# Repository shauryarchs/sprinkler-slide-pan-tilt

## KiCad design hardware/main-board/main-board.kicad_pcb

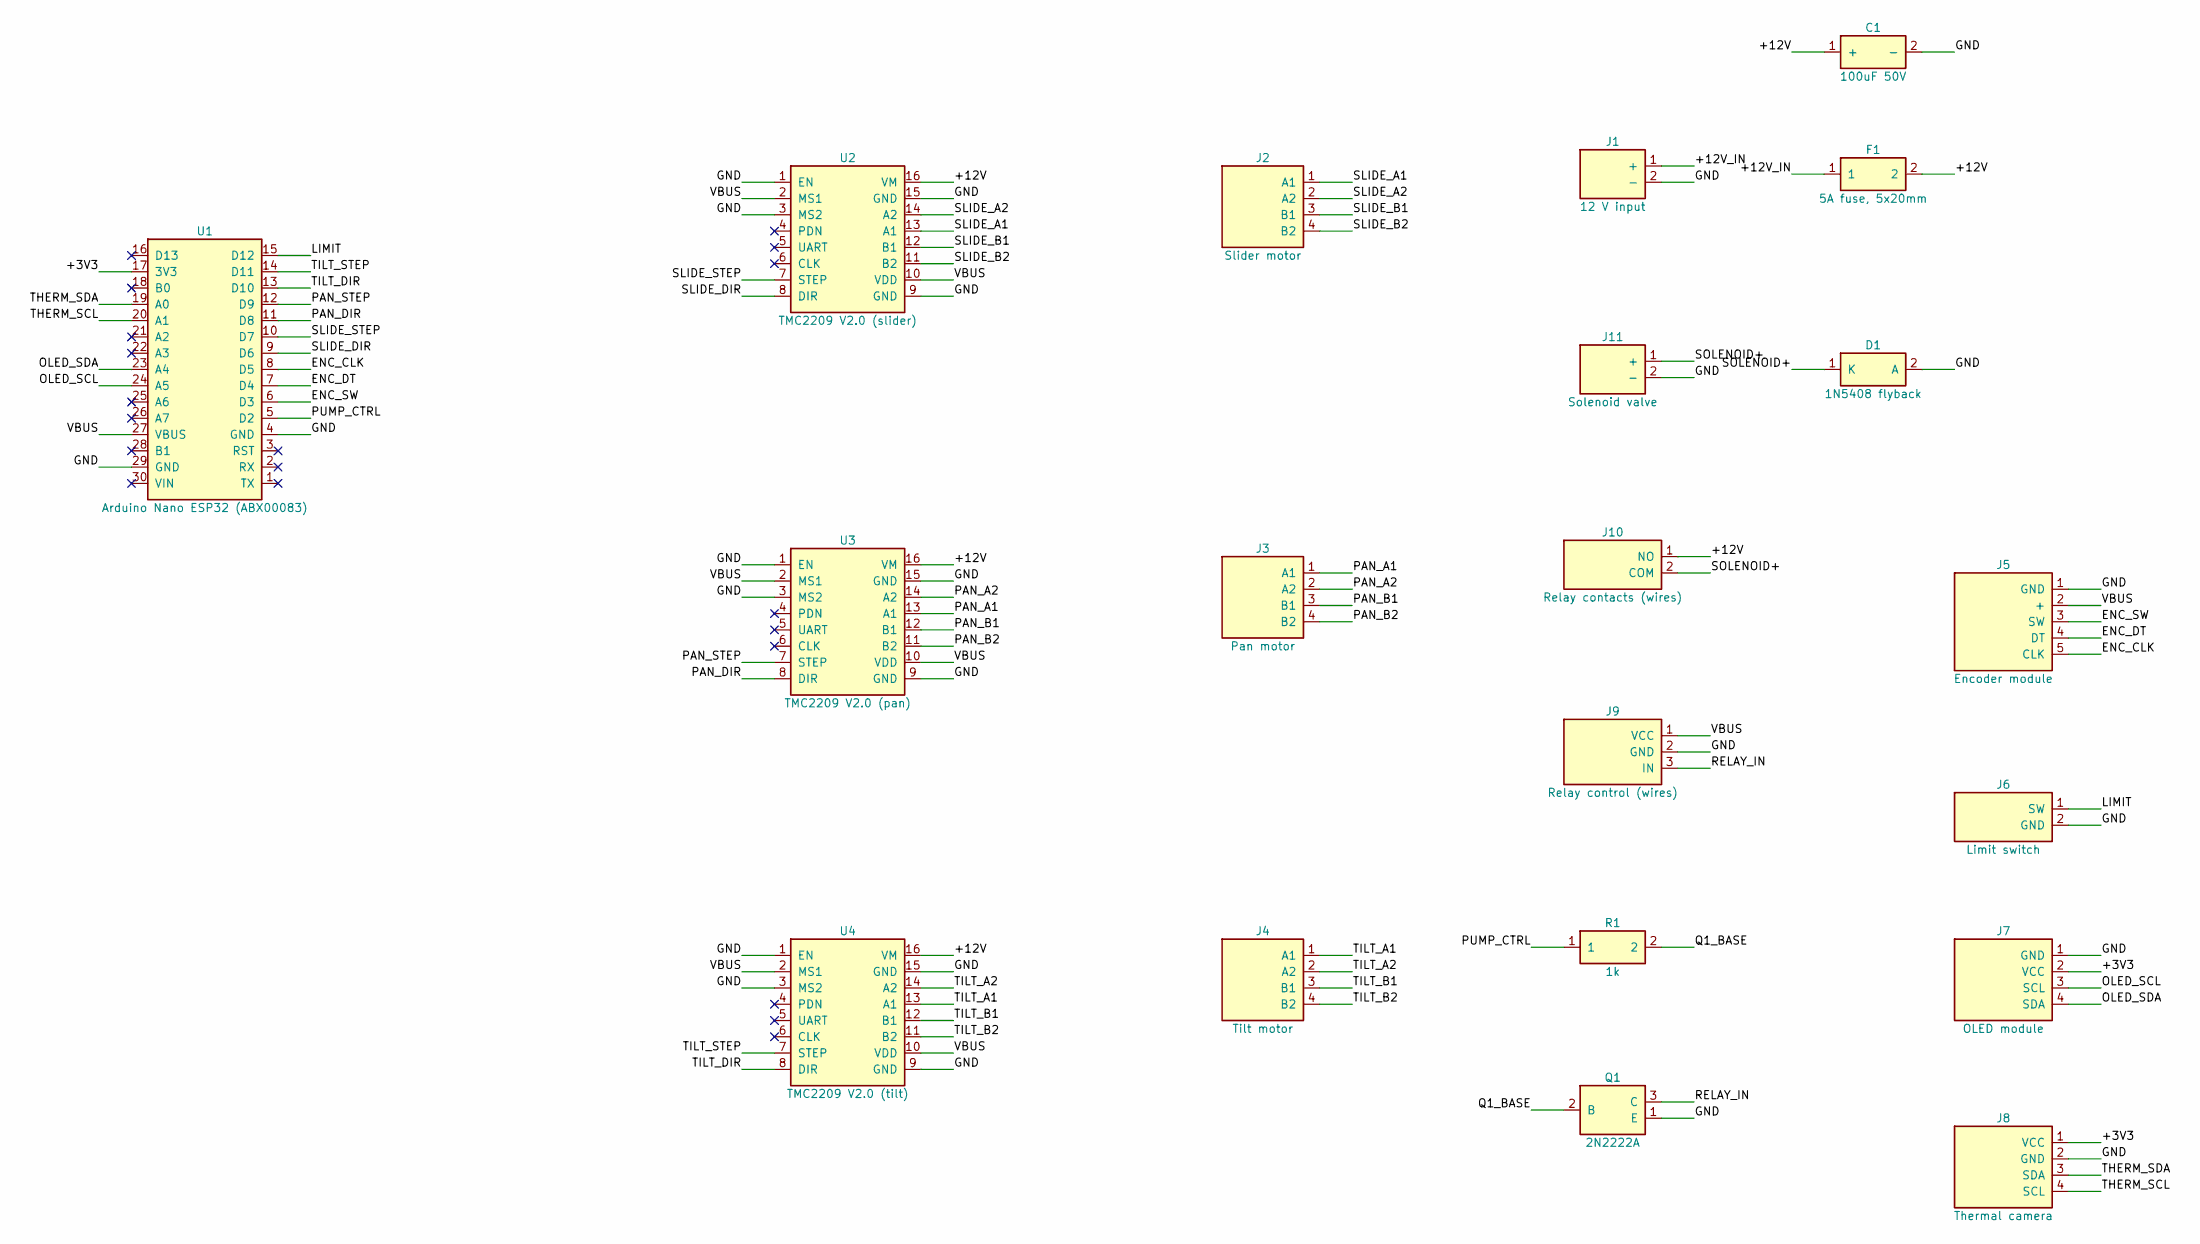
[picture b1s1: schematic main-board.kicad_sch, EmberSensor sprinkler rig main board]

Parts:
C1: 100uF 50V; CP_Radial_D8.0mm_P3.50mm
D1: 1N5408 flyback; D_DO-201AD_P15.24mm_Horizontal
F1: 5A fuse, 5x20mm; Fuseholder_Clip-5x20mm_Keystone_3517_Inline_P23.11x6.76mm_D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
J1: 12 V input; TerminalBlock_Phoenix_MKDS-1,5-2-5.08_1x02_P5.08mm_Horizont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
J2: Slider motor; TerminalBlock_Phoenix_MKDS-1,5-4-5.08_1x04_P5.08mm_Horizont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
J3: Pan motor; TerminalBlock_Phoenix_MKDS-1,5-4-5.08_1x04_P5.08mm_Horizont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
J4: Tilt motor; TerminalBlock_Phoenix_MKDS-1,5-4-5.08_1x04_P5.08mm_Horizont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
J5: Encoder module; PinHeader_1x05_P2.54mm_Vertical
J6: Limit switch; JST_XH_B2B-XH-A_1x02_P2.50mm_Vertical
J7: OLED module; PinHeader_1x04_P2.54mm_Vertical
J8: Thermal camera; JST_XH_B4B-XH-A_1x04_P2.50mm_Vertical
J9: Relay control (wires); PinHeader_1x03_P2.54mm_Vertical
J10: Relay contacts (wires); TerminalBlock_Phoenix_MKDS-1,5-2-5.08_1x02_P5.08mm_Horizont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
J11: Solenoid valve; TerminalBlock_Phoenix_MKDS-1,5-2-5.08_1x02_P5.08mm_Horizont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
Q1: 2N2222A; TO-92_Inline_Wide
R1: 1k; R_Axial_DIN0207_L6.3mm_D2.5mm_P10.16mm_Horizontal
U1: Arduino Nano ESP32 (ABX00083); Arduino_Nano
U2: TMC2209 V2.0 (slider); Pololu_Breakout-16_15.2x20.3mm
U3: TMC2209 V2.0 (pan); Pololu_Breakout-16_15.2x20.3mm
U4: TMC2209 V2.0 (tilt); Pololu_Breakout-16_15.2x20.3mm

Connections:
/+3V3: J7.2 (VCC), J8.1 (VCC), U1.17 (3V3)
/+12V: C1.1 (+), F1.2, J10.1 (NO), U2.16 (VM), U3.16 (VM), U4.16 (VM)
/+12V_IN: F1.1, J1.1 (+)
/ENC_CLK: J5.5 (CLK), U1.8 (D5)
/ENC_DT: J5.4 (DT), U1.7 (D4)
/ENC_SW: J5.3 (SW), U1.6 (D3)
/GND: C1.2 (-), D1.2 (A), J1.2 (-), J5.1 (GND), J6.2 (GND), J7.1 (GND), J8.2 (GND), J9.2 (GND), J11.2 (-), Q1.1 (E), U1.4 (GND), U1.29 (GND), U2.1 (EN), U2.3 (MS2), U2.9 (GND), U2.15 (GND), U3.1 (EN), U3.3 (MS2), U3.9 (GND), U3.15 (GND), U4.1 (EN), U4.3 (MS2), U4.9 (GND), U4.15 (GND)
/LIMIT: J6.1 (SW), U1.15 (D12)
/OLED_SCL: J7.3 (SCL), U1.24 (A5)
/OLED_SDA: J7.4 (SDA), U1.23 (A4)
/PAN_A1: J3.1 (A1), U3.13 (A1)
/PAN_A2: J3.2 (A2), U3.14 (A2)
/PAN_B1: J3.3 (B1), U3.12 (B1)
/PAN_B2: J3.4 (B2), U3.11 (B2)
/PAN_DIR: U1.11 (D8), U3.8 (DIR)
/PAN_STEP: U1.12 (D9), U3.7 (STEP)
/PUMP_CTRL: R1.1, U1.5 (D2)
/Q1_BASE: Q1.2 (B), R1.2
/RELAY_IN: J9.3 (IN), Q1.3 (C)
/SLIDE_A1: J2.1 (A1), U2.13 (A1)
/SLIDE_A2: J2.2 (A2), U2.14 (A2)
/SLIDE_B1: J2.3 (B1), U2.12 (B1)
/SLIDE_B2: J2.4 (B2), U2.11 (B2)
/SLIDE_DIR: U1.9 (D6), U2.8 (DIR)
/SLIDE_STEP: U1.10 (D7), U2.7 (STEP)
/SOLENOID+: D1.1 (K), J10.2 (COM), J11.1 (+)
/THERM_SCL: J8.4 (SCL), U1.20 (A1)
/THERM_SDA: J8.3 (SDA), U1.19 (A0)
/TILT_A1: J4.1 (A1), U4.13 (A1)
/TILT_A2: J4.2 (A2), U4.14 (A2)
/TILT_B1: J4.3 (B1), U4.12 (B1)
/TILT_B2: J4.4 (B2), U4.11 (B2)
/TILT_DIR: U1.13 (D10), U4.8 (DIR)
/TILT_STEP: U1.14 (D11), U4.7 (STEP)
/VBUS: J5.2 (+), J9.1 (VCC), U1.27 (VBUS), U2.2 (MS1), U2.10 (VDD), U3.2 (MS1), U3.10 (VDD), U4.2 (MS1), U4.10 (VDD)

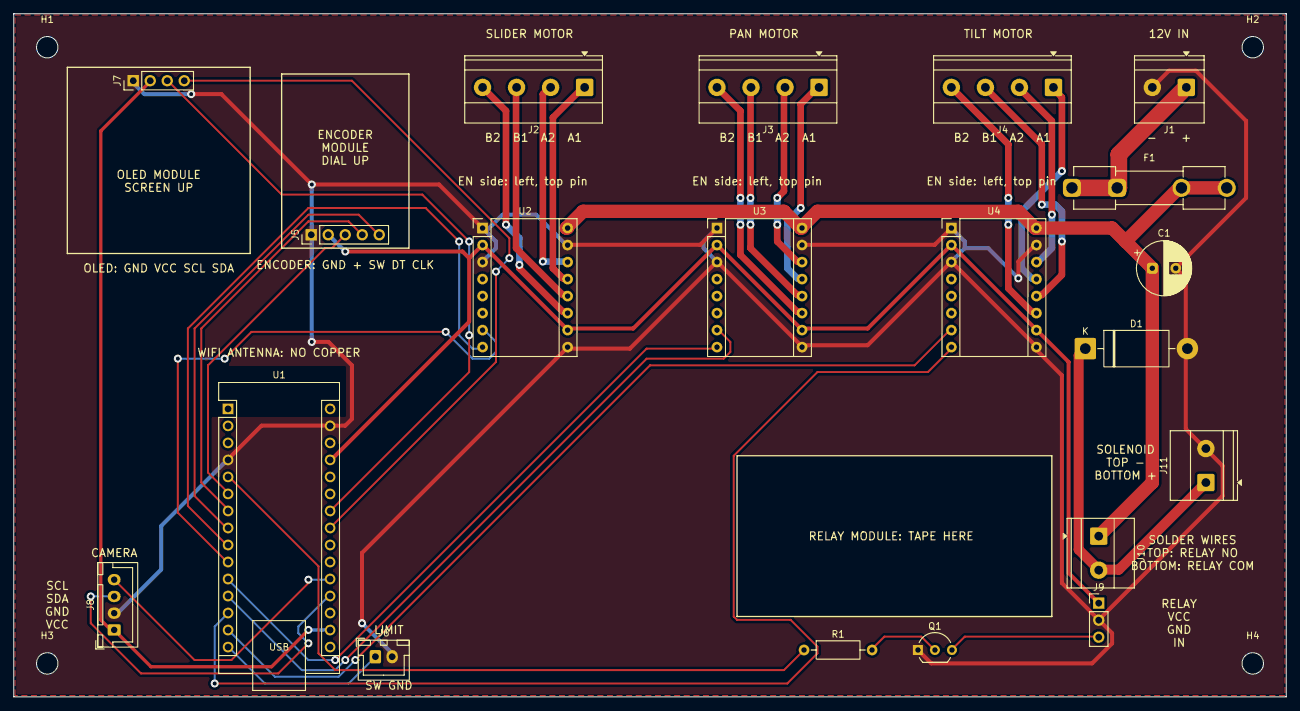
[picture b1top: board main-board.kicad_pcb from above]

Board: 2 copper layers, 190.0 x 102.0 mm, 24 parts (0 on the bottom side), 35 nets.

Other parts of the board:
H1, H2, H3, H4: MountingHole_3.2mm_M3

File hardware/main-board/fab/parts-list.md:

# Main board parts list

All parts are through-hole and hand-soldered. "Have" means the part already runs on the breadboard rig.

| Ref | Part | Qty | Have / buy | Notes |
|---|---|---|---|---|
| U1 | Arduino Nano ESP32 (ABX00083) | 1 | Have | Solder in, or use 2x 1x15 female headers (2.54 mm) to keep it removable |
| U2-U4 | TMC2209 V2.0 StepStick (Teyleten) | 3 | Have | 6x 1x8 female headers (2.54 mm) recommended so drivers can be swapped and Vref adjusted |
| J7 | 0.96 in SSD1306 OLED (Hosyond) | 1 | Have | Solders in by its own pins; foam tape under the far edge |
| J5 | KY-040 encoder (WMYCONGCONG) | 1 | Have | Pins bent straight; solders in by its own pins; foam tape under the far edge |
| C1 | 100 uF 50 V electrolytic | 1 | Have | 8 mm body, 3.5 mm lead spacing; long lead (+) to the square pad |
| R1 | 1 kOhm resistor | 1 | Have | |
| Q1 | 2N2222A NPN (TO-92) | 1 | Have | Holes are E, B, C left to right with the flat face toward the board's bottom edge. Check your transistor's markings: some TO-92 2N2222A parts are C, B, E |
| - | Relay module (AEDIKO, SRD-05VDC-SL-C) | 1 | Have | Foam-taped in the marked area; VCC/GND/IN wires to J9, NO/COM wires to J10 |
| D1 | 1N5408 diode | 1 | Buy | Stripe (cathode) to the square pad marked K |
| F1 | Keystone 3517 5x20 mm fuse clip | 2 | Buy | Use this exact clip (DigiKey 36-3517-ND); other clips have different pin spacing |
| F1 | 5 A fuse, 5x20 mm | 1 + spares | Buy | Fast-blow glass |
| J1, J11 | Wires soldered direct | - | - | 12 V jack leads and solenoid wires solder into the 1.3 mm holes; the screw-terminal footprint is only the hole pattern |
| J2-J4 | Wires soldered direct | - | - | Motor jumper wires solder into the 1.3 mm holes; unplug the motors at the jumper joints |
| J6 | Wires soldered direct | - | - | Limit switch jumper wires solder into the 1.0 mm holes; unplug at the halfway extension joint |
| J8 | Wires soldered direct | - | - | Thermal camera jumper wires solder into the 0.95 mm holes; unplug at the halfway extension joint |
| J9 | Solder pads | - | - | Relay VCC, GND, IN wires solder straight in |
| J10 | Solder pads | - | - | Relay NO, COM wires solder straight in |
| H1-H4 | M3 standoffs and screws | 4 | Optional | Board corners |

Only the fuse, the fuse clips, and the diode need to be bought. Every wire soldered straight to the board
needs strain relief (a zip tie or hot glue near the joint) so flexing doesn't break it at the solder. The
12 V input wires carry up to about 4 A, so use 18 AWG or thicker there, not thin jumper wire.

## Board order settings

Upload `main-board-gerbers.zip`. Settings: 2 layers, 190 x 102 mm, 1.6 mm FR-4, 1 oz copper
(2 oz is better for the 12 V traces if it costs little extra), HASL finish, any solder mask color.

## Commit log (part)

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2026-04-26 Add .gitignore for macOS, IntelliJ, Maven/Java, codegen, and local artifacts
2026-04-26 added CLAUDE.md
2026-04-26 added arduino source for testing
2026-04-26 fixed folder structure
2026-04-26 Update idle screen hint to 'r=run smooth'
2026-04-26 Add I2C scanner sketch for diagnosing OLED bus issues
2026-04-26 Add button (D4/D5/D6) and pot (A0) motor controls
    - Three buttons with INPUT_PULLUP and 30 ms debounce: D4 CCW, D5 CW, D6 stop
    - Pot on A0 drives speed and direction when motor is IDLE; 25-count deadband
    - Mid-spin direction reversals re-ramp to avoid losing steps
    - Display shows POT/SMOOTH/DANCE/IDLE with speed bar and CW/CCW indicator
    - Boot prints initial button pin states to surface miswiring early
    - OLED redraws throttled to ~10 fps during pot sliding to spare I2C bandwidth
2026-04-26 Convert pot to positional encoder (1° pot = 1° motor) and add doggy idle art
    - Pot now reports a signed step delta per poll instead of a velocity target;
    motor steps once per delta, so turning the knob rotates the motor 1:1 in
    degrees and stopping the knob stops the motor
    - Pot is still active only when motor is IDLE; setMode() resyncs the pot's
    reference on entry to IDLE so the motor doesn't lurch to catch up with
    pot movement that happened during SMOOTH/DANCE
2026-04-26 Add running dog animation, 10x pot range, 3x smooth speed, THEO label
    - Display: 4-frame running-dog ASCII animation (~7 fps) plays whenever the
    motor is rotating (SMOOTH/DANCE/POT). IDLE keeps the static dog.
    - IDLE label renamed to THEO.
    - Pot: STEPS_PER_FULL_POT 200 -> 2000, so a full knob turn drives ten
    motor revolutions instead of one. Conversion simplified to use the
    step count directly (no degree math). Wiring header updated.
2026-04-26 Stop pot motor immediately when knob stops turning
    Process pot delta in small batches (8 steps) and re-poll between them
    instead of committing the full delta to a tight step loop. When the pot
    goes stationary, the next pollDelta returns 0 and runPot exits — the
    motor stops within ~one batch (~8 ms) of the user releasing the knob
    instead of running off the remaining backlog. Trade-off: a very fast
    knob sweep can leave the motor a few steps behind the pot's final
2026-04-26 Make STOP button override pot tracking with a latch
    Previously pressing STOP while the pot was driving the motor was a
    no-op (mode was already IDLE). Now STOP latches a potDisabled flag that
    runPot checks each iteration, so the motor stops within one batch
    regardless of whether SMOOTH/DANCE or pot tracking caused the motion.
    - Motor::stopPressed() halts and sets the latch; pressing STOP again
    while already idle toggles the latch back off so the pot can be
2026-04-27 Switch smooth mode to single-interval pulse timing
    - Replace half-period delay + ramp-up with one full-period interval
    - Drop unused setMode() from public Motor API
    - Update comments to reflect TB6600 driver wiring
2026-04-27 Add joystick Y-axis control with deflection-based speed
    - New joystick module reads A0, emits up/down/center events with deadband
    - Joystick mirrors CW/CCW/STOP buttons for direction
    - Deflection magnitude maps to step interval via Motor::setSpeedFraction
    - Light push = slow, full push = fast; centered stick leaves speed alone
2026-05-09 unknown change
2026-05-09 Add TMC2209 stepper slider sketch with pot, OLED, and limit-switch homing
2026-05-09 Move DIR/STEP pins to D6/D7 to free interrupt pins D2/D3
2026-05-09 Add motor 2 oscillator on D8/D9 sweeping 0-180 degrees, paused by D10 button
2026-05-13 Replace pot/LED/pause-button with KY-040 encoder; SW jogs CW at homing speed
    Pinout changes:
    - ENCODER_SW=D3, ENCODER_DT=D4, ENCODER_CLK=D5 (DT/CLK declared, unused)
    - LIMIT_PIN moved from D4 to D10
    - LED_PIN/BUTTON_PIN/POT_PIN removed
    Behavior:
    - Holding the encoder switch jogs the carriage CW at HOMING_STEP_INTERVAL_US
2026-05-13 Drive motor speed and direction from KY-040 dial position
    Encoder dial maps to a signed setpoint in [-20, +20]: sign picks direction
    (positive = CW, negative = CCW), magnitude scales the step interval
    linearly from 3000 us at |dial|=1 down to 120 us at |dial|=20. Dial at 0
    stops the motor. SW press resets the dial to 0 for an immediate stop.
    Encoder reading is interrupt-driven on ENCODER_CLK falling edge with a
    1.5 ms software debounce; running off an ISR keeps detents from being
2026-05-14 Fix step-pulse starvation, home-switch rest, and encoder reset race
    - Bump displayInterval from 100 ms to 250 ms; the ~30 ms blocking
    display.display() call was consuming ~30% of stepping time and
    causing audible jitter at high dial values.
    - Back off the carriage after homing until the limit switch releases,
    plus 80 microsteps (~0.5 mm) of clearance, before zeroing position.
    Prevents the switch from re-tripping on drift.
2026-05-14 Add long-press re-home, two-pass homing, OLED fallback, misc cleanup
    - Long-press SW (>=1.5 s) now triggers a full re-home; short press still
    acts as an immediate stop. Detaches the encoder ISR during the rehome
    to ignore dial spins, then re-zeros encoderPos under a critical section.
    - Two-pass homing: fast CCW approach, back off past the switch, slow CCW
    re-engage for an accurate trip point, final back off with clearance.
    Reduces switch wear and improves home repeatability.
2026-05-14 Rename first-motor sketch to main and move into arduino-source/main
    Arduino IDE expects the .ino filename to match its parent folder, so
    arduino-source/main/main.ino is the canonical location for this sketch.
2026-05-14 Refactor sketch into per-component classes
    Split the single-file sketch into one class per hardware component, with
    main.ino reduced to instantiation and orchestration. Behavior is intended
    to be equivalent to the prior single-file version.
    New modules (sketch-folder .h/.cpp pairs, all compiled into the sketch):
    - LimitSwitch: pull-up + engaged() reader for the home switch.
    - StatusLed: non-blocking 1 Hz heartbeat for the onboard LED.
2026-05-14 Remove StatusLed component
    The board no longer has the onboard LED wired up for status indication,
    so the heartbeat-on-OLED-missing path is dead weight. Delete StatusLed.h
    and StatusLed.cpp, and remove the instance, begin(), setBlinking() and
    update() calls from main.ino. The OLED-missing fallback still works —
    Display::showStatus() and showHomingMessage() are no-ops when begin()
    reports failure, so the motor keeps running without any UI.
2026-05-14 Use Arduino-ESP32 v2.x timer API in Stepper::begin()
    The board package installed is esp32 core 2.0.18 (timerBegin takes
    timer index + divider + countUp; alarm is set with timerAlarmWrite +
    timerAlarmEnable). The v3.x single-frequency signature I had used
    doesn't exist on this core. Switched to the v2.x form:
    timerBegin(0, 80, true) // 80 MHz / 80 = 1 MHz
    timerAttachInterrupt(t, cb, true) // edge-triggered
2026-05-14 Drop speed readout from the display
    The speed line is no longer wanted on the OLED, so remove the
    "S:NN.Nmm/s" segment from Display::showStatus and switch the position
    back to the more readable "Pos: NN mm" form now that the line has room.
    Also tear out the now-dead plumbing rather than leave unused parameters:
    - Display::showStatus loses its spdTenths parameter.
    - Stepper::currentSpeedTenthsMmPerSec() and the lastTargetInterval_ /
2026-05-14 Auto-reset the dial to 0 when carriage reaches max travel
    At kMaxPositionSteps (1000 mm) with the dial still in CW territory,
    reset encoderPos to 0 in the main loop. The motor doesn't move (edge
    guard already blocked it), but the dial is now logically neutral, so
    the next CCW click registers as -1 and starts reverse motion
    immediately — no need to wind back through 0 by hand.
    If the user keeps dialing CW at max, each tick gets reset on the next
2026-05-14 Move limit switch from D10 to D12
    Frees D10 and D11 on the Arduino Nano ESP32 for other uses. The limit
    switch only needs INPUT_PULLUP + a falling/level read, which any ESP32-S3
    GPIO supports, so D12 is a drop-in replacement.
2026-05-14 Add Motor2 + motor-selection menu
    A second TMC2209-driven stepper is wired on DIR=D8 / STEP=D9. Motor1's
    DIR/STEP, limit switch and homing/long-press-rehome behavior are
    unchanged. The encoder now drives a small mode machine:
    Menu rotation scrolls between "Motor 1" / "Motor 2"
    tap (release < kLongPressMs) selects highlighted item
    Motor1Control existing dial-driven speed + edge guards
2026-05-14 Drop display refresh interval from 250 ms to 100 ms
    The 250 ms interval was sized for the pre-timer-driven stepper, when
    display.display()'s ~30 ms blocking I2C frame transfer would starve
    step pulses. Step generation now runs from a hardware-timer ISR, so
    the display block no longer pauses the motor — the 250 ms ceiling on
    visual lag (felt as a delay between turning the dial and the screen
    catching up) is no longer worth the trade.
2026-05-14 Add Motor3 (DIR=D10, STEP=D11) and extend the selection menu
    A third TMC2209-driven stepper, behaviourally identical to Motor2:
    bounded to [0°, 180°], no limit switch, no homing — must be aligned
    to 0° before power-on. Lives in its own class (Motor3.h/.cpp) and
    owns ESP32 hardware timer 2 (Stepper has 0, Motor2 has 1, timer 3
    still free).
    main.ino:
2026-05-14 Rename Stepper class and file to Motor1
    Bring the slide motor's class name in line with Motor2 and Motor3.
    - Stepper.h -> Motor1.h, Stepper.cpp -> Motor1.cpp (git tracked as
    renames, content otherwise unchanged).
    - class Stepper -> class Motor1; all member-function definitions,
    static instance pointer, and the four static_asserts updated.
    - main.ino: #include 'Motor1.h', global is now Motor1 motor1(...),
2026-05-14 Rename motor classes by role: Slider/Pan/Tilt
    Motor1 -> SliderMotor1 (the 1 m slide)
    Motor2 -> PanMotor2 (pan, 0-180°)
    Motor3 -> TiltMotor3 (tilt, 0-180°)
    - Files renamed (git tracks as renames at ~90% similarity):
    Motor1.{h,cpp} -> SliderMotor1.{h,cpp}
    Motor2.{h,cpp} -> PanMotor2.{h,cpp}
2026-05-14 Use Slider/Pan/Tilt names on the display
    - Menu lists 'Slider-Motor1', 'Pan-Motor2', 'Tilt-Motor3' instead of
    'Motor 1/2/3'. Reverted the menu font back to size 1 because the
    new names don't fit at size 2 ('> Slider-Motor1' is 15 chars =
    180 px wide vs the 128 px panel).
    - Motor 2 / Motor 3 status footers updated to 'Pan-Motor2 [0-180]'
    and 'Tilt-Motor3 [0-180]'.
2026-05-16 Extend Pan/Tilt motor range to 360 degrees
2026-05-16 Add All Motors demo mode
2026-05-16 Bound Pan/Tilt to +/-360 and oscillate them in All Motors mode
2026-05-16 Bound Pan to +/-105, add post-home Pan/Tilt zero-position setup
2026-05-16 Push device state to embersensor.com/api/motor/state
2026-05-18 implemented command-poller
2026-05-18 Honor setSliderSpeed in Motor 1/2/3 modes, not just All Motors
    dispatchRemoteCommand previously gated setSliderSpeed on
    Mode::AllMotorsControl, so clicking Motor 1/2/3 on the website left
    the motor stationary even when a remote setSliderSpeed arrived: the
    device just dropped it. Expand the gate to cover Motor1Control,
    Motor2Control, Motor3Control and AllMotorsControl, which is exactly
    the set of modes where the encoder dial represents a speed setpoint.
2026-05-20 Accept setAllMotorsPanSpeed / setAllMotorsTiltSpeed remote commands
    Convert kAllMotorsPanSpeed / kAllMotorsTiltSpeed from compile-time
    constants to runtime-mutable variables so the website can retune the
    Pan/Tilt bounce magnitudes in All Motors mode. The slider already had
    this via the encoder dial; Pan/Tilt now have parity. Values are clamped
    to [0, Encoder::kRange] in the dispatcher.
2026-05-20 Rename All Motors to Petrol and stop driving tilt in that mode
    The demo mode shown in the menu and on the website is now labeled
    Petrol. Internally the mode key stays "allmotors" so the wire protocol
    is unchanged. The tilt motor no longer bounces in this mode — only the
    slider and pan motors do. Tilt is moved exclusively by the calibration
    commands (nudgeTilt / zeroTilt). The setAllMotorsTiltSpeed remote
    command and its firmware plumbing are removed.
